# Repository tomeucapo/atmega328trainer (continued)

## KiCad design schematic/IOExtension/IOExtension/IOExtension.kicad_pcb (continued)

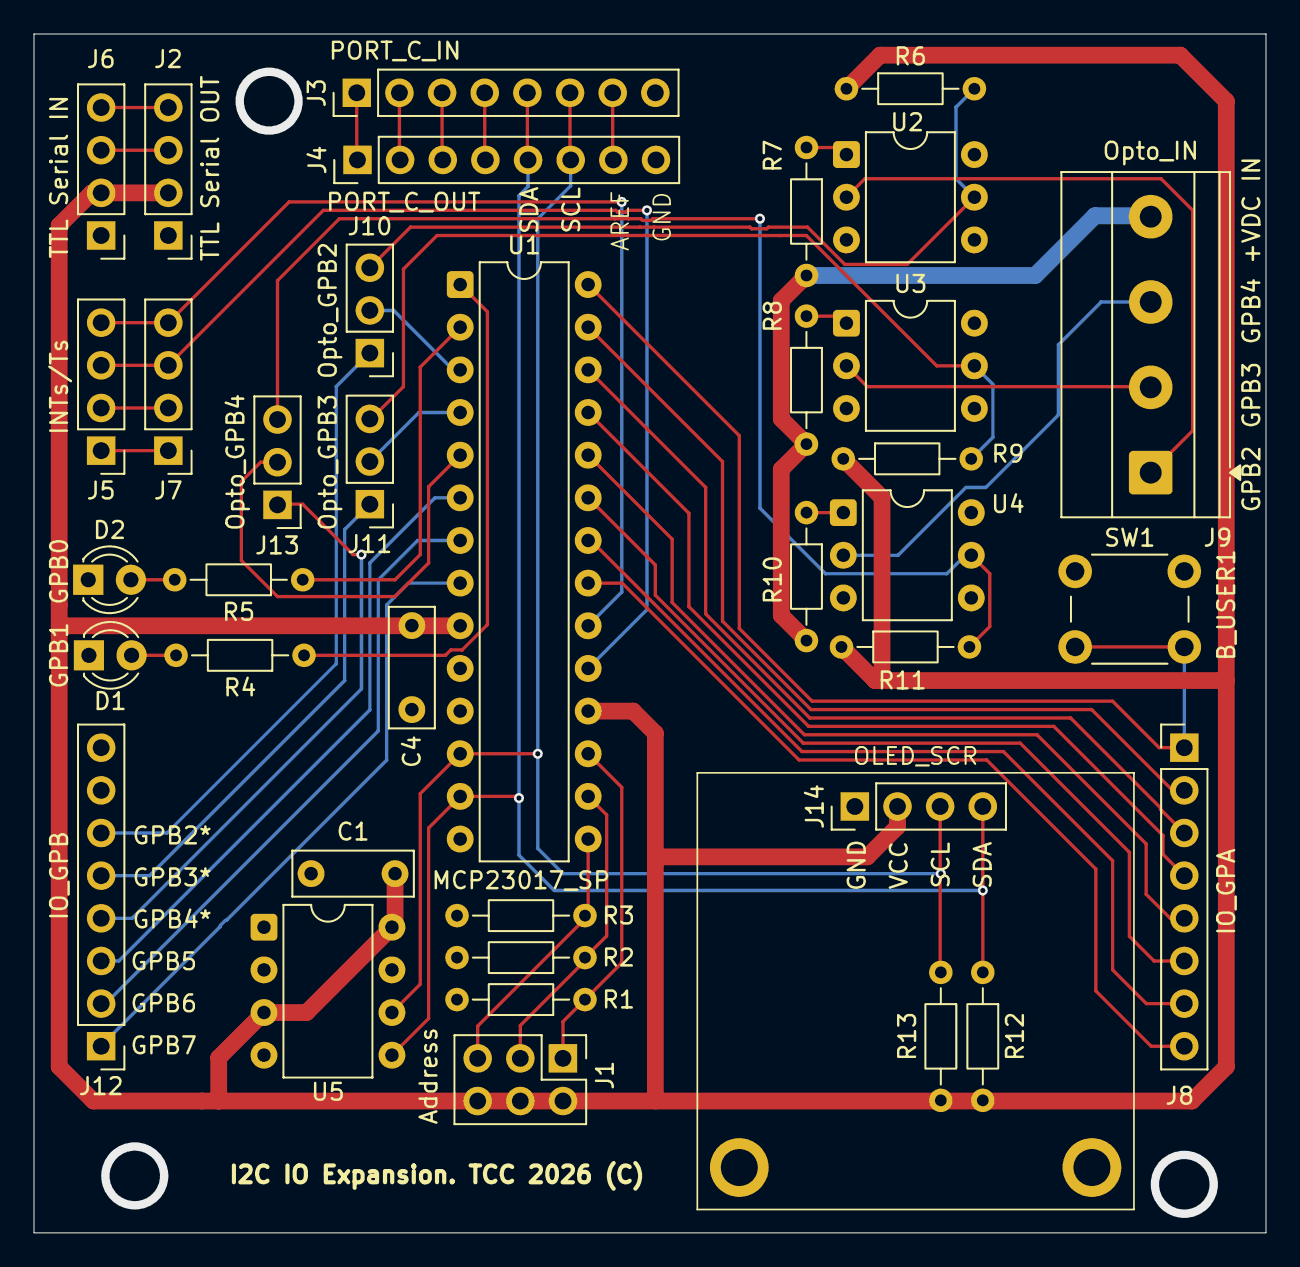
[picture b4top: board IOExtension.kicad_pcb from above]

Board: 2 copper layers, 73.4 x 71.4 mm, 39 parts (0 on the bottom side), 49 nets.

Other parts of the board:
GND: MountingHole_2.2mm_M2_ISO7380_Pad
GND#2: MountingHole_2.2mm_M2_ISO7380_Pad

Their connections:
GND: GND.1, GND#2.1; also elsewhere on the board

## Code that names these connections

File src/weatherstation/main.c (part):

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#define BTN_MCP_PORT MCP23017_PORTA
#define BTN_MCP_PIN 7

// LED GPB0 del MCP23017: replica el parpadeo de PD6
static volatile uint8_t mcp_led_state = 0;
static uint8_t mcp_present = 0;

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
// ======================================================
// PLUVIOMETRO
// PB1 = PCINT1
// CONTACTO NC
// ======================================================

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}

// LED GPB0 del MCP23017: se actualiza desde el estado que togglea
// la ISR de TIMER0 junto con PD6 (1 Hz).
static void task_mcp_led(void)
{
    static uint8_t last_state = 0;
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    twi_bus_recover();
    _delay_ms(150);

    // MCP23017 (PC4=SDA, PC5=SCL). mcp23017_init() ya deja GPA7 como
    // entrada (pulsador a masa) y el resto como salidas.
    mcp23017_init();
    mcp23017_pullup(MCP23017_PORTA, (1 << BTN_MCP_PIN)); // pull-up en GPA7
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    bme_present = bme280_init();
    pred_init();

    // Nodo remoto LoRa (SX1276/78 por SPI en PD2=CS, PD3=RESET)
    lora_present = sx127x_init();

    welcome();
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
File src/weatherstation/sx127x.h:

#ifndef SX127X_H
#define SX127X_H

#include <stdint.h>

// ======================================================
// SX1276/77/78/79 (RFM95W / Ra-02) en modo LoRa punto a punto.
// SPI: PB3=MOSI, PB4=MISO, PB5=SCK. CS y RESET se definen aqui.
// El modulo debe alimentarse a 3.3 V (el ATmega de 5 V necesita
// level shifting en las lineas SPI o un modulo con regulador).
// ======================================================

#ifndef SX127X_FREQ_HZ
#define SX127X_FREQ_HZ 868000000UL   // RFM95W UE (Ra-02: 433000000UL)
#endif

// CS en PD2, RESET en PD3 (libres en el header J7 si no se usa
// la IOExtension). CS debe tener pull-up externo a 3.3 V.
#define SX127X_CS_DDR   DDRD
#define SX127X_CS_PORT  PORTD
#define SX127X_CS_BIT   PD2

#define SX127X_RST_DDR  DDRD
#define SX127X_RST_PORT PORTD
#define SX127X_RST_BIT  PD3

#define SX127X_MAX_PAYLOAD 64

// Devuelve 1 si el chip responde (RegVersion valido) y queda en RX.
uint8_t sx127x_init(void);

// Deja el radio en recepcion continua.
void sx127x_set_rx(void);

// Duerme el radio (bajo consumo entre transmisiones del nodo).
void sx127x_sleep(void);

// Transmite un paquete (max. SX127X_MAX_PAYLOAD) y vuelve a RX.
// Devuelve 1 si se completo el TxDone.
uint8_t sx127x_send(const uint8_t *data, uint8_t len);

// Saca un paquete si ya llego. Devuelve 1 y actualiza *len.
uint8_t sx127x_poll_rx(uint8_t *buf, uint8_t *len);

#endif

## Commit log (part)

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2026-02-16 Initial schematics push
2026-02-16 added source code
2026-02-18 Added CMakeLists.txt and some VSCode settings
2026-02-18 Removed build dir
2026-02-18 removed unnecessary build dir
